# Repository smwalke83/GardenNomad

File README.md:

The Garden Nomad is a garden monitoring system that monitors local environmental data - as well as having a deployable digital PH meter - and sends it to the cloud. This project was done for the CNM Ingenuity IoT Bootcamp. It is the capstone project. In this repository you will find all of the documentation for this project. You will see six different folders here:

Code - This contains all of the coding I did for this project. There are several test code files, as well as the final code.

Proposal - Contains the original project proposal.

Drawings, Notes, and Flowcharts - Contains everything that was in my notebook at the end of this project. Conceptual drawings, measurements, notes, flowcharts, etc.

Fritzing - Contains the wiring schematic and breadboard fritzing files.

Garden Nomad PCB - Contains the files for the Printed Curcuit Board design.

Solidworks and Other Design - Contains all the Solidworks files for the 3D printed housing design, as well as an Adobe Illustrator file for the acrylic piece that was cut on the laser cutter.

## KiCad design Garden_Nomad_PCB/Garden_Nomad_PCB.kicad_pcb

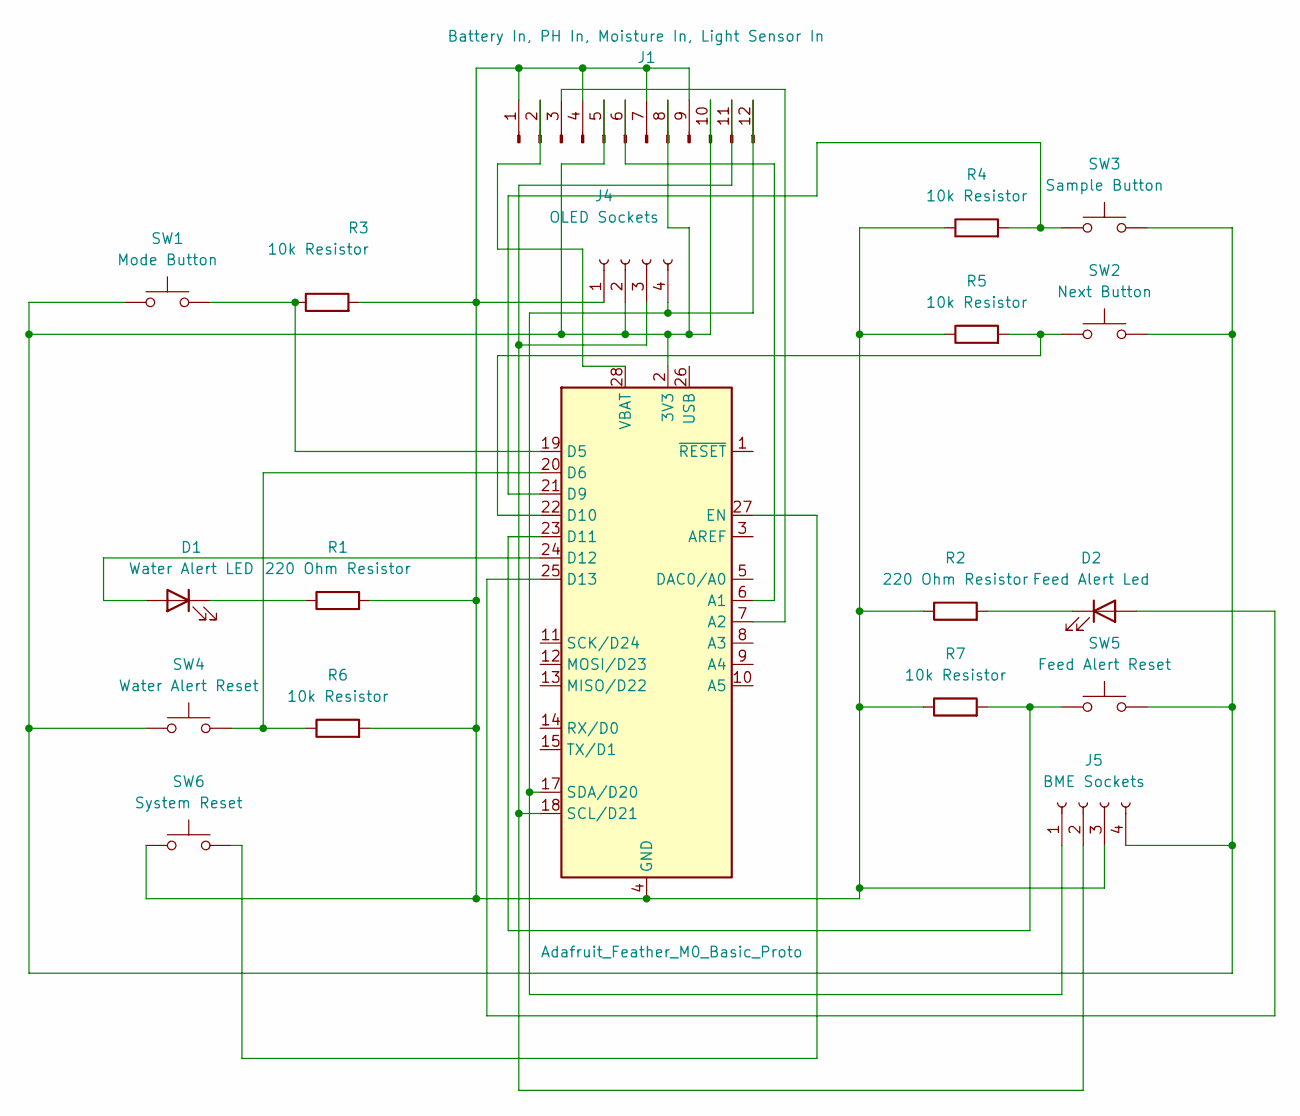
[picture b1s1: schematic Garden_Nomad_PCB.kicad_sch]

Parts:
A1: Adafruit_Feather_M0_Basic_Proto; Adafruit_Feather
D1: Water Alert LED; LED_D3.0mm
D2: Feed Alert Led; LED_D3.0mm
J1: Battery In, PH In, Moisture In, Light Sensor In; PinHeader_1x12_P2.54mm_Horizontal
J4: OLED Sockets; PinSocket_1x04_P2.54mm_Vertical
J5: BME Sockets; PinSocket_1x04_P2.54mm_Vertical
R1, R2: 220 Ohm Resistor; R_Axial_DIN0204_L3.6mm_D1.6mm_P5.08mm_Horizontal
R3, R4, R5, R6, R7: 10k Resistor; R_Axial_DIN0204_L3.6mm_D1.6mm_P5.08mm_Horizontal
SW1: Mode Button; SW_PUSH_6mm_H5mm
SW2: Next Button; SW_PUSH_6mm_H5mm
SW3: Sample Button; SW_PUSH_6mm_H5mm
SW4: Water Alert Reset; SW_PUSH_6mm_H5mm
SW5: Feed Alert Reset; SW_PUSH_6mm_H5mm
SW6: System Reset; SW_PUSH_6mm_H5mm

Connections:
unnamed: A1.2 (3V3), J1.5, J1.8, J1.10, J4.2, J5.4, SW1.1, SW2.2, SW3.2, SW4.1, SW5.2
unnamed: A1.6 (A1), J1.6
unnamed: A1.7 (A2), J1.3
unnamed: A1.19 (D5), R3.1, SW1.2
unnamed: A1.20 (D6), R6.1, SW4.2
unnamed: A1.21 (D9), R4.2, SW3.1
unnamed: A1.22 (D10), R5.2, SW2.1
unnamed: A1.23 (D11), R7.2, SW5.1
unnamed: A1.24 (D12), D1.2 (A)
unnamed: A1.25 (D13), D2.2 (A)
unnamed: A1.27 (EN), SW6.2
unnamed: A1.18 (SCL/D21), J1.11, J4.3, J5.2
unnamed: A1.17 (SDA/D20), J1.12, J4.4, J5.1
unnamed: A1.28 (VBAT), J1.2
unnamed: D1.1 (K), R1.1
unnamed: D2.1 (K), R2.2
unnamed: A1.4 (GND), A1.16 (GND), J1.1, J1.4, J1.7, J1.9, J4.1, J5.3, R1.2, R2.1, R3.2, R4.1, R5.1, R6.2, R7.1, SW6.1

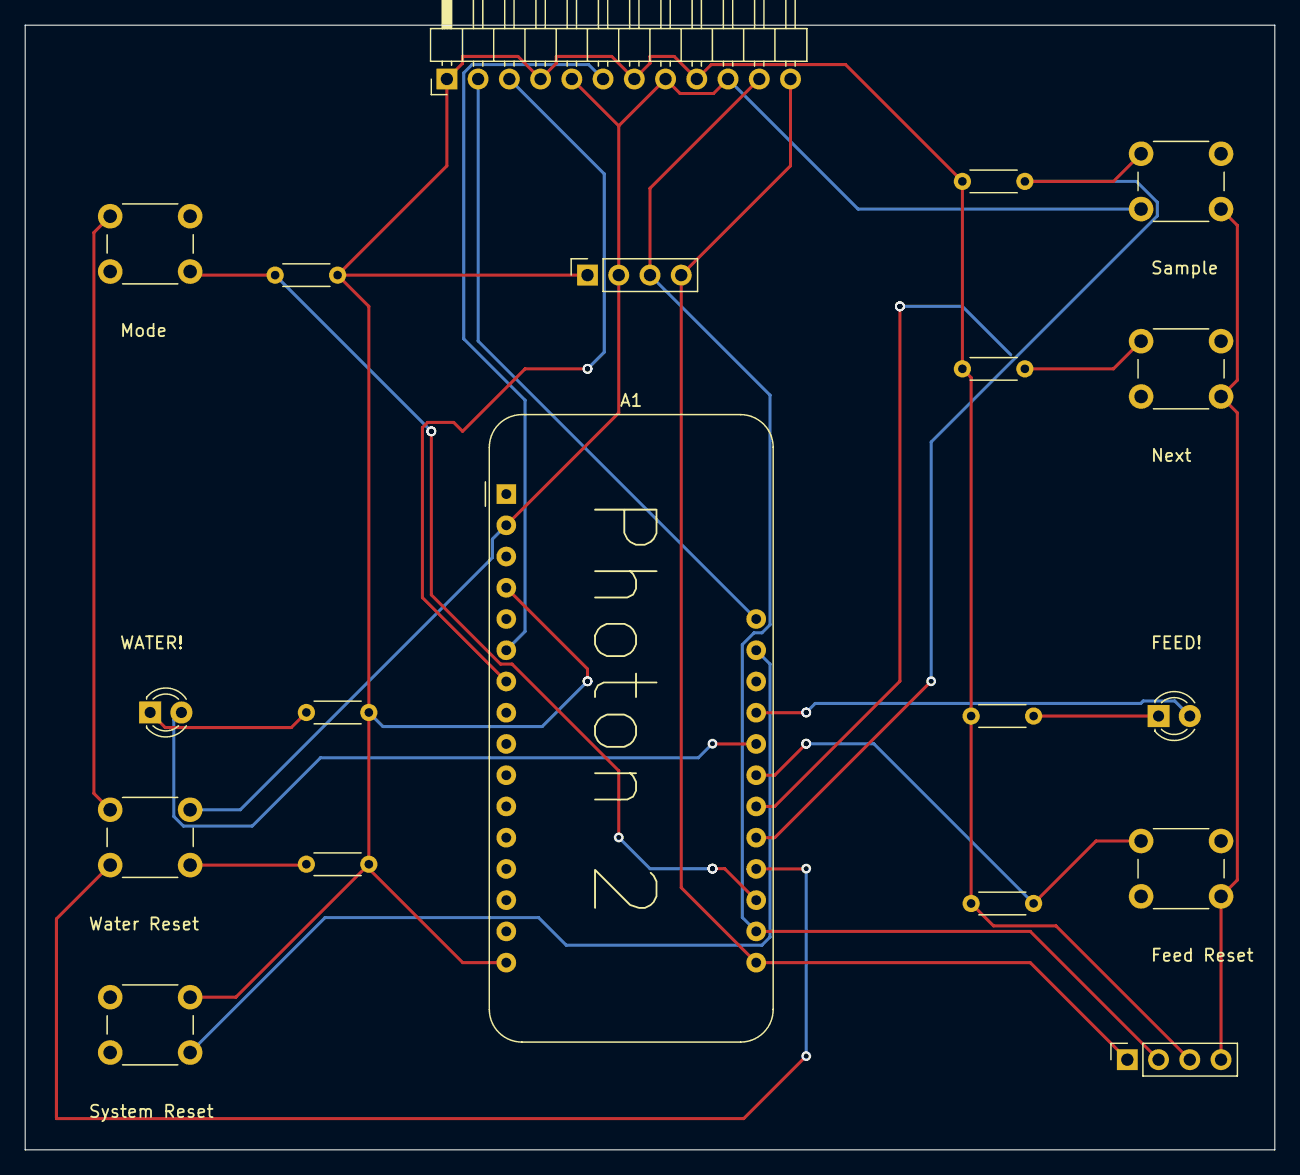
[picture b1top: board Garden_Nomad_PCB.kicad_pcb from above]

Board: 2 copper layers, 101.6 x 91.4 mm, 19 parts (0 on the bottom side), 17 nets.

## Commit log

2024-04-19 Added liscense and proposal
2024-04-19 Added flowcharts
2024-04-19 PH Calibrated and working
2024-04-19 Calibrating/testing light sensor
2024-04-19 Designed initial body/case
2024-04-19 Organizing files and folders
2024-04-19 Placeholder text in README
2024-04-19 Moved files again
2024-04-26 Fritzing, Hinge Design, PH Probe Housing Design
2024-04-26 Fritzing schematic
2024-05-02 Fixed .gitignore
2024-05-02 Wrote most of the code, needs testing
2024-05-02 Tweaking code - still untested
2024-05-02 more tinkering - still needs testing
2024-05-03 Most of the code working, light sensor library may be causing problems
2024-05-03 Solved light sensor, code working, just need MQTT, sleep mode
2024-05-03 Code is close - need Node Red MQTT
2024-05-10 Code is working, more 3D designs, Laser cutter design
2024-05-14 Commented code, lowered sleep duration (for now), added PDFs of all notes, finished PCB
2024-05-16 pushing anything I missed
2024-05-16 ReadMe updated
